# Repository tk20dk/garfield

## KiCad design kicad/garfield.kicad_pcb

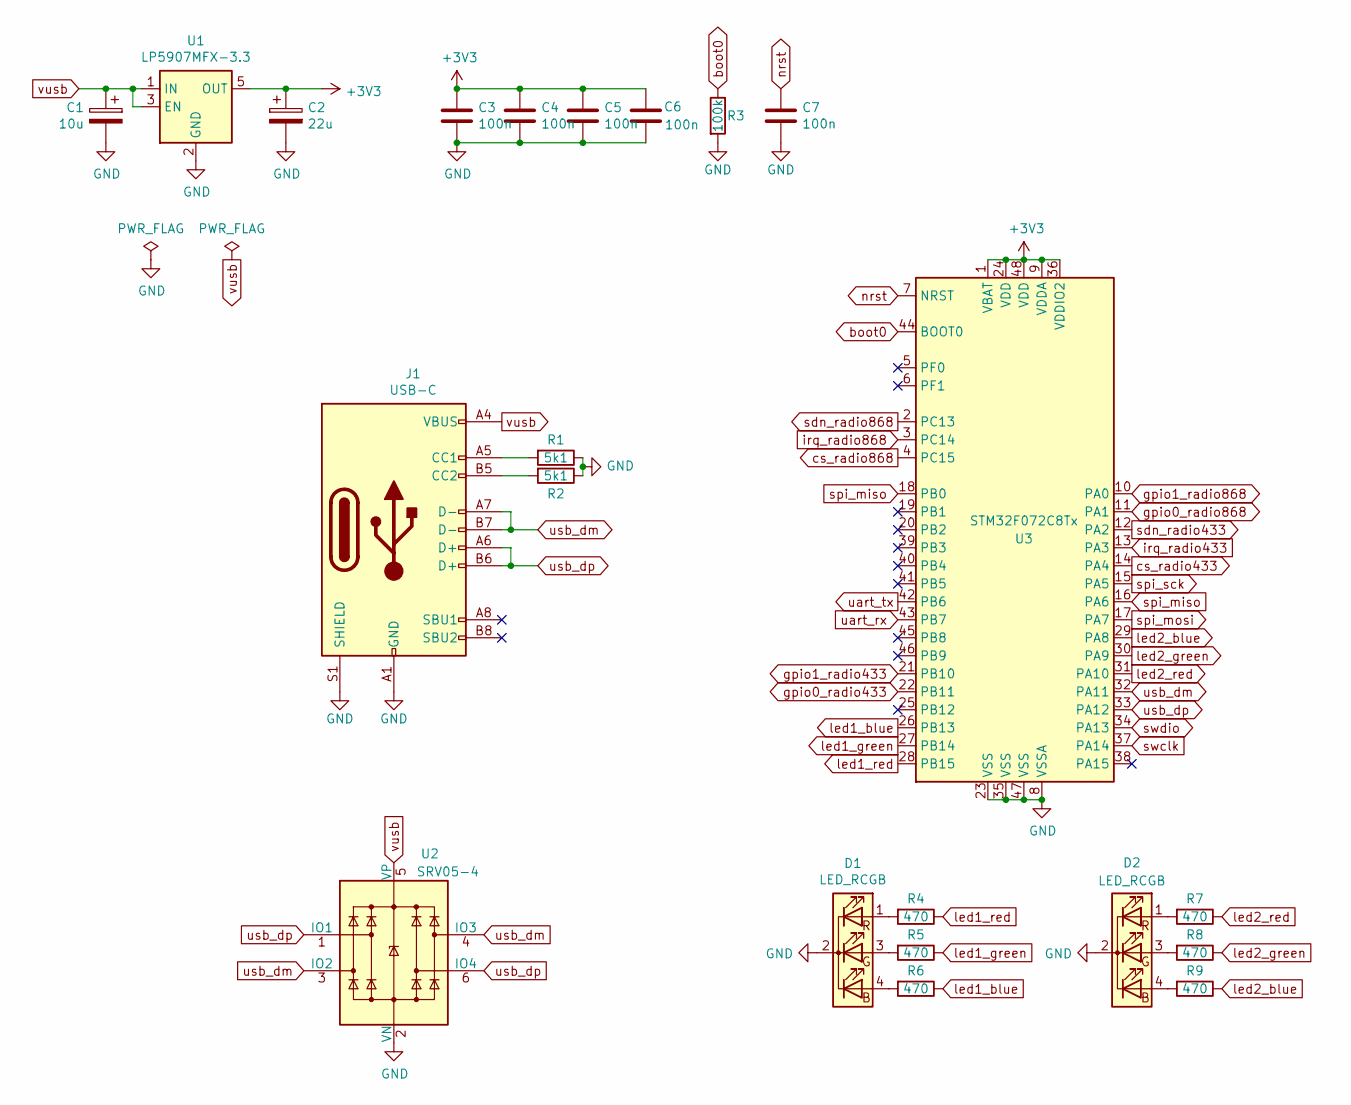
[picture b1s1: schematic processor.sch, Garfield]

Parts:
C1: 10u; CP_EIA-3528-12_Kemet-T
C2: 22u; CP_EIA-3528-12_Kemet-T
C3, C4, C5, C6, C7: 100n; C_0603_1608Metric
D1, D2: LED_RCGB; LED_D5.0mm-4
J1: USB-C; USB_C_Receptacle_HRO_TYPE-C-31-M-12
R1, R2: 5k1; R_0603_1608Metric
R3: 100k; R_0603_1608Metric
R4, R5, R6, R7, R8, R9: 470; R_0603_1608Metric
U1: LP5907MFX-3.3; SOT-23-5
U2: SRV05-4; SOT-23-6
U3: STM32F072C8Tx; LQFP-48_7x7mm_P0.5mm

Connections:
GND: C1.2, C2.2, C3.2, C4.2, C5.2, C6.2, C7.2, D1.2 (K), D2.2 (K), J1.A1 (GND), J1.A12 (GND), J1.B1 (GND), J1.B12 (GND), J1.S1 (SHIELD), R1.1, R2.1, R3.2, U1.2 (GND), U2.2 (VN), U3.8 (VSSA), U3.23 (VSS), U3.35 (VSS), U3.47 (VSS); also elsewhere on the board
unnamed: D1.1 (RA), R4.2
unnamed: D1.3 (GA), R5.2
unnamed: D1.4 (BA), R6.2
unnamed: D2.1 (RA), R7.2
unnamed: D2.3 (GA), R8.2
unnamed: D2.4 (BA), R9.2
unnamed: J1.A5 (CC1), R1.2
unnamed: J1.B5 (CC2), R2.2
boot0: R3.1, U3.44 (BOOT0)
cs_radio433: U3.14 (PA4); also elsewhere on the board
cs_radio868: U3.4 (PC15); also elsewhere on the board
gpio0_radio433: U3.22 (PB11); also elsewhere on the board
gpio0_radio868: U3.11 (PA1); also elsewhere on the board
gpio1_radio433: U3.21 (PB10); also elsewhere on the board
gpio1_radio868: U3.10 (PA0); also elsewhere on the board
irq_radio433: U3.13 (PA3); also elsewhere on the board
irq_radio868: U3.3 (PC14); also elsewhere on the board
led1_blue: R6.1, U3.26 (PB13)
led1_green: R5.1, U3.27 (PB14)
led1_red: R4.1, U3.28 (PB15)
led2_blue: R9.1, U3.29 (PA8)
led2_green: R8.1, U3.30 (PA9)
led2_red: R7.1, U3.31 (PA10)
nrst: C7.1, U3.7 (NRST)
sdn_radio433: U3.12 (PA2); also elsewhere on the board
sdn_radio868: U3.2 (PC13); also elsewhere on the board
spi_miso: U3.16 (PA6), U3.18 (PB0); also elsewhere on the board
spi_mosi: U3.17 (PA7); also elsewhere on the board
spi_sck: U3.15 (PA5); also elsewhere on the board
swclk: U3.37 (PA14); also elsewhere on the board
swdio: U3.34 (PA13); also elsewhere on the board
uart_rx: U3.43 (PB7); also elsewhere on the board
uart_tx: U3.42 (PB6); also elsewhere on the board
usb_dm: J1.A7 (D-), J1.B7 (D-), U2.3 (IO2), U2.4 (IO3), U3.32 (PA11)
usb_dp: J1.A6 (D+), J1.B6 (D+), U2.1 (IO1), U2.6 (IO4), U3.33 (PA12)
vusb: C1.1, J1.A4 (VBUS), J1.A9 (VBUS), J1.B4 (VBUS), J1.B9 (VBUS), U1.1 (IN), U1.3 (EN), U2.5 (VP)

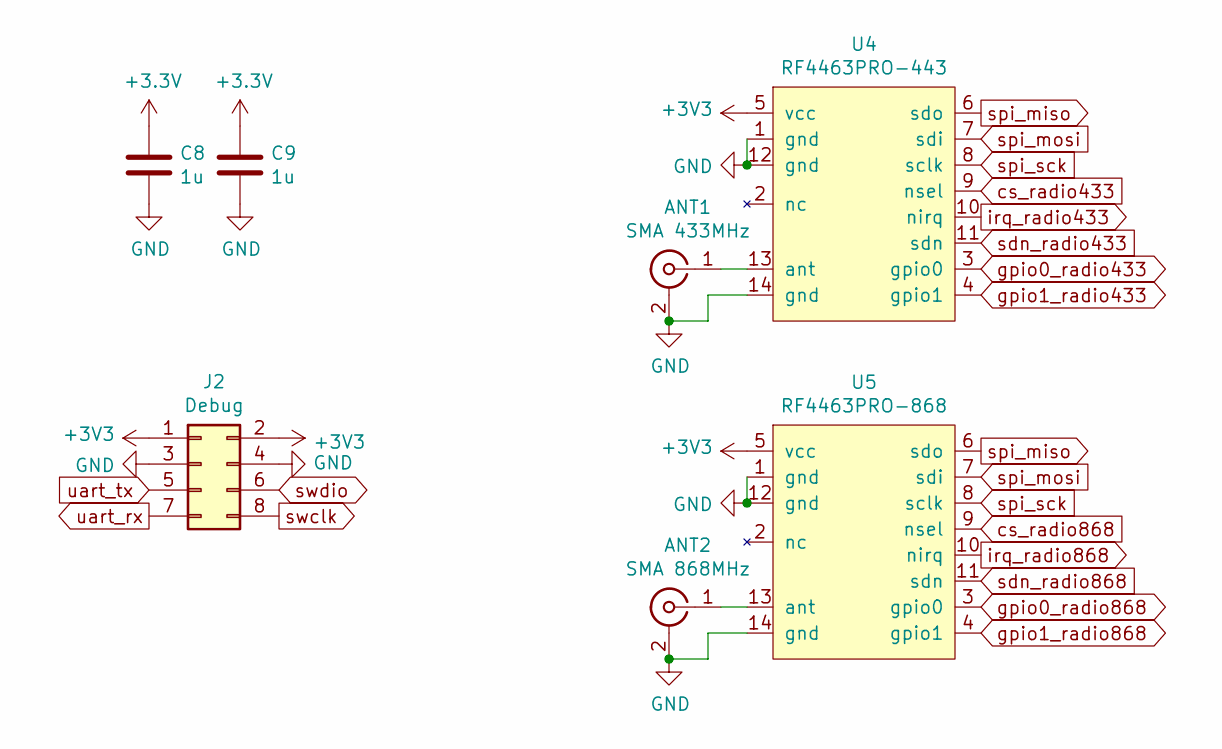
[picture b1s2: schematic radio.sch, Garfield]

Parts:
ANT1: SMA 433MHz; SMA_Molex_73251-2200_Horizontal
ANT2: SMA 868MHz; SMA_Molex_73251-2200_Horizontal
C8, C9: 1u; C_0805_2012Metric
J2: Debug; PinHeader_2x04_P2.54mm_Vertical
U4: RF4463PRO-443; RF4462PRO
U5: RF4463PRO-868; RF4462PRO

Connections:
GND: ANT1.2 (Ext), ANT2.2 (Ext), C8.2, C9.2, J2.3, J2.4, U4.1 (gnd), U4.12 (gnd), U4.14 (gnd), U5.1 (gnd), U5.12 (gnd), U5.14 (gnd); also elsewhere on the board
unnamed: ANT1.1 (In), U4.13 (ant)
unnamed: ANT2.1 (In), U5.13 (ant)
cs_radio433: U4.9 (nsel); also elsewhere on the board
cs_radio868: U5.9 (nsel); also elsewhere on the board
gpio0_radio433: U4.3 (gpio0); also elsewhere on the board
gpio0_radio868: U5.3 (gpio0); also elsewhere on the board
gpio1_radio433: U4.4 (gpio1); also elsewhere on the board
gpio1_radio868: U5.4 (gpio1); also elsewhere on the board
irq_radio433: U4.10 (nirq); also elsewhere on the board
irq_radio868: U5.10 (nirq); also elsewhere on the board
sdn_radio433: U4.11 (sdn); also elsewhere on the board
sdn_radio868: U5.11 (sdn); also elsewhere on the board
spi_miso: U4.6 (sdo), U5.6 (sdo); also elsewhere on the board
spi_mosi: U4.7 (sdi), U5.7 (sdi); also elsewhere on the board
spi_sck: U4.8 (sclk), U5.8 (sclk); also elsewhere on the board
swclk: J2.8; also elsewhere on the board
swdio: J2.6; also elsewhere on the board
uart_rx: J2.7; also elsewhere on the board
uart_tx: J2.5; also elsewhere on the board

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
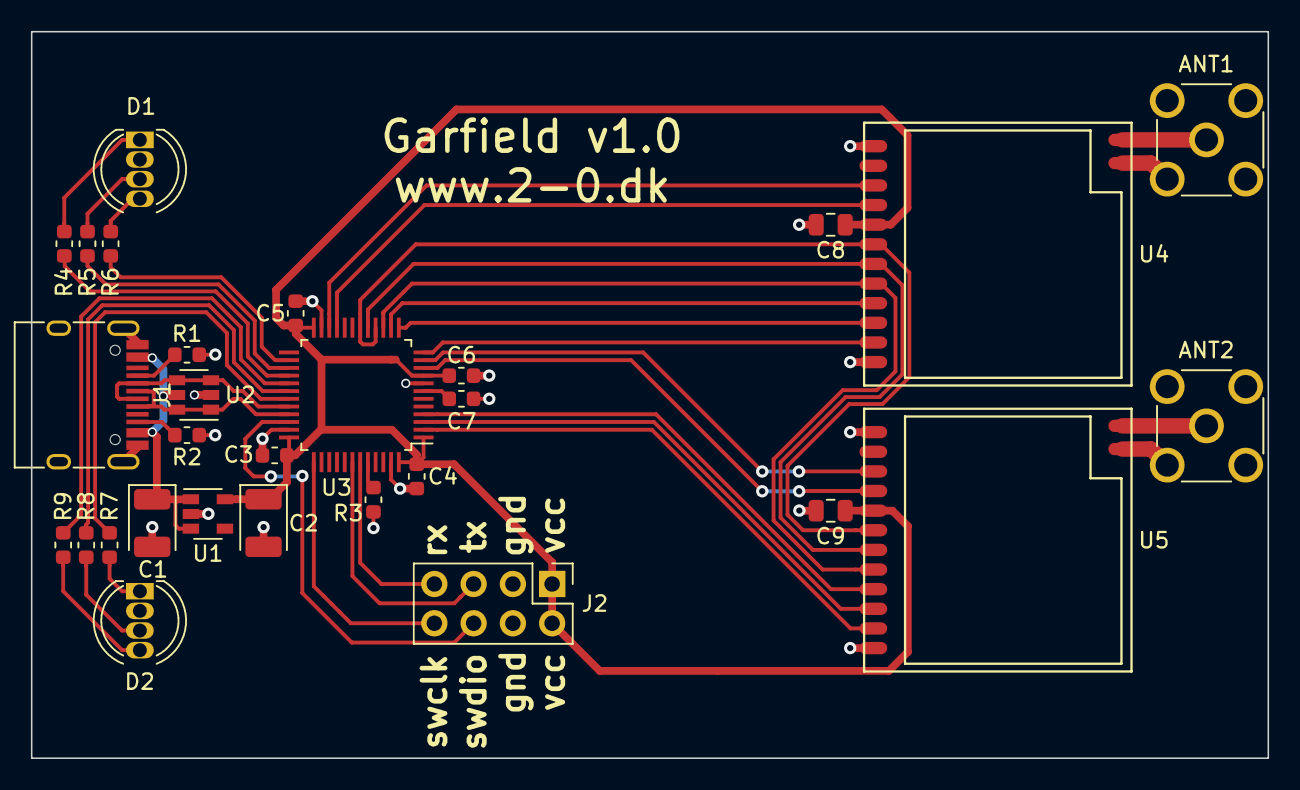
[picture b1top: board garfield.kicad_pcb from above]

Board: 2 copper layers, 80.0 x 47.0 mm, 29 parts (0 on the bottom side), 40 nets.

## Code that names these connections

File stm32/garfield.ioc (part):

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Mcu.Name=STM32F072C(8-B)Tx
Mcu.Package=LQFP48
Mcu.UserName=STM32F072C8Tx
PA0.GPIOParameters=GPIO_PuPd,GPIO_Label
PA0.GPIO_Label=GPIO1_RADIO868
PA0.GPIO_PuPd=GPIO_PULLUP
PA0.Signal=GPIO_Input
PA1.GPIOParameters=GPIO_PuPd,GPIO_Label
PA1.GPIO_Label=GPIO0_RADIO868
PA1.GPIO_PuPd=GPIO_PULLUP
PA1.Signal=GPIO_Input
PA10.GPIOParameters=GPIO_Label
PA10.GPIO_Label=LED2_RED
PA10.Signal=GPIO_Output
PA11.Mode=Device
PA11.Signal=USB_DM
PA12.Mode=Device
PA12.Signal=USB_DP
PA13.Mode=Serial_Wire
PA13.Signal=SYS_SWDIO
PA14.Mode=Serial_Wire
PA14.Signal=SYS_SWCLK
PA2.GPIOParameters=GPIO_Label
PA2.GPIO_Label=SDN_RADIO433
PA2.Signal=GPIO_Output
PA3.GPIOParameters=GPIO_PuPd,GPIO_Label,GPIO_ModeDefaultEXTI
PA3.GPIO_Label=IRQ_RADIO433
PA3.GPIO_ModeDefaultEXTI=GPIO_MODE_IT_FALLING
PA3.GPIO_PuPd=GPIO_PULLUP
PA3.Signal=GPXTI3
PA4.GPIOParameters=PinState,GPIO_Label
PA4.GPIO_Label=CS_RADIO433
PA4.PinState=GPIO_PIN_SET
PA4.Signal=GPIO_Output
PA5.Mode=Full_Duplex_Master
PA5.Signal=SPI1_SCK
PA6.GPIOParameters=GPIO_PuPd
PA6.GPIO_PuPd=GPIO_PULLUP
PA6.Mode=Full_Duplex_Master
PA6.Signal=SPI1_MISO
PA7.Mode=Full_Duplex_Master
PA7.Signal=SPI1_MOSI
PA8.GPIOParameters=GPIO_Label
PA8.GPIO_Label=LED2_BLUE
PA8.Signal=GPIO_Output
PA9.GPIOParameters=GPIO_Label
PA9.GPIO_Label=LED2_GREEN
PA9.Signal=GPIO_Output
PB0.GPIOParameters=GPIO_Label
PB0.GPIO_Label=SPI__MISO
PB0.Signal=GPIO_Input
PB10.GPIOParameters=GPIO_PuPd,GPIO_Label
PB10.GPIO_Label=GPIO1_RADIO433
PB10.GPIO_PuPd=GPIO_PULLUP
PB10.Signal=GPIO_Input
PB11.GPIOParameters=GPIO_PuPd,GPIO_Label
PB11.GPIO_Label=GPIO0_RADIO433
PB11.GPIO_PuPd=GPIO_PULLUP
PB11.Signal=GPIO_Input
PB13.GPIOParameters=GPIO_Label
PB13.GPIO_Label=LED1_BLUE
PB13.Signal=GPIO_Output
PB14.GPIOParameters=GPIO_Label
PB14.GPIO_Label=LED1_GREEN
PB14.Signal=GPIO_Output
PB15.GPIOParameters=GPIO_Label
PB15.GPIO_Label=LED1_RED
PB15.Signal=GPIO_Output
PB6.GPIOParameters=GPIO_Speed,GPIO_Label
PB6.GPIO_Label=UART_TX
PB6.GPIO_Speed=GPIO_SPEED_FREQ_LOW
PB6.Mode=Asynchronous
PB6.Signal=USART1_TX
PB7.GPIOParameters=GPIO_Speed,GPIO_PuPd,GPIO_Label
PB7.GPIO_Label=UART_RX
PB7.GPIO_PuPd=GPIO_PULLUP
PB7.GPIO_Speed=GPIO_SPEED_FREQ_LOW
PB7.Mode=Asynchronous
PB7.Signal=USART1_RX
PC13.GPIOParameters=GPIO_Label
PC13.GPIO_Label=SDN_RADIO868
PC13.Signal=GPIO_Output
PC14-OSC32_IN.GPIOParameters=GPIO_PuPd,GPIO_Label,GPIO_ModeDefaultEXTI
PC14-OSC32_IN.GPIO_Label=IRQ_RADIO868
PC14-OSC32_IN.GPIO_ModeDefaultEXTI=GPIO_MODE_IT_FALLING
PC14-OSC32_IN.GPIO_PuPd=GPIO_PULLUP
PC14-OSC32_IN.Signal=GPXTI14
PC15-OSC32_OUT.GPIOParameters=PinState,GPIO_Label
PC15-OSC32_OUT.GPIO_Label=CS_RADIO868
PC15-OSC32_OUT.PinState=GPIO_PIN_SET
PC15-OSC32_OUT.Signal=GPIO_Output
RCC.SYSCLKFreq_VALUE=48000000
RCC.SYSCLKSource=RCC_SYSCLKSOURCE_HSI48
board=custom

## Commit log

2020-11-19 created initial kicad and stm32 projects
